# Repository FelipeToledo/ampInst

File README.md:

ampInst
=======

Repo para una placa amplificadora de bajo ruido para su uso en sismografos

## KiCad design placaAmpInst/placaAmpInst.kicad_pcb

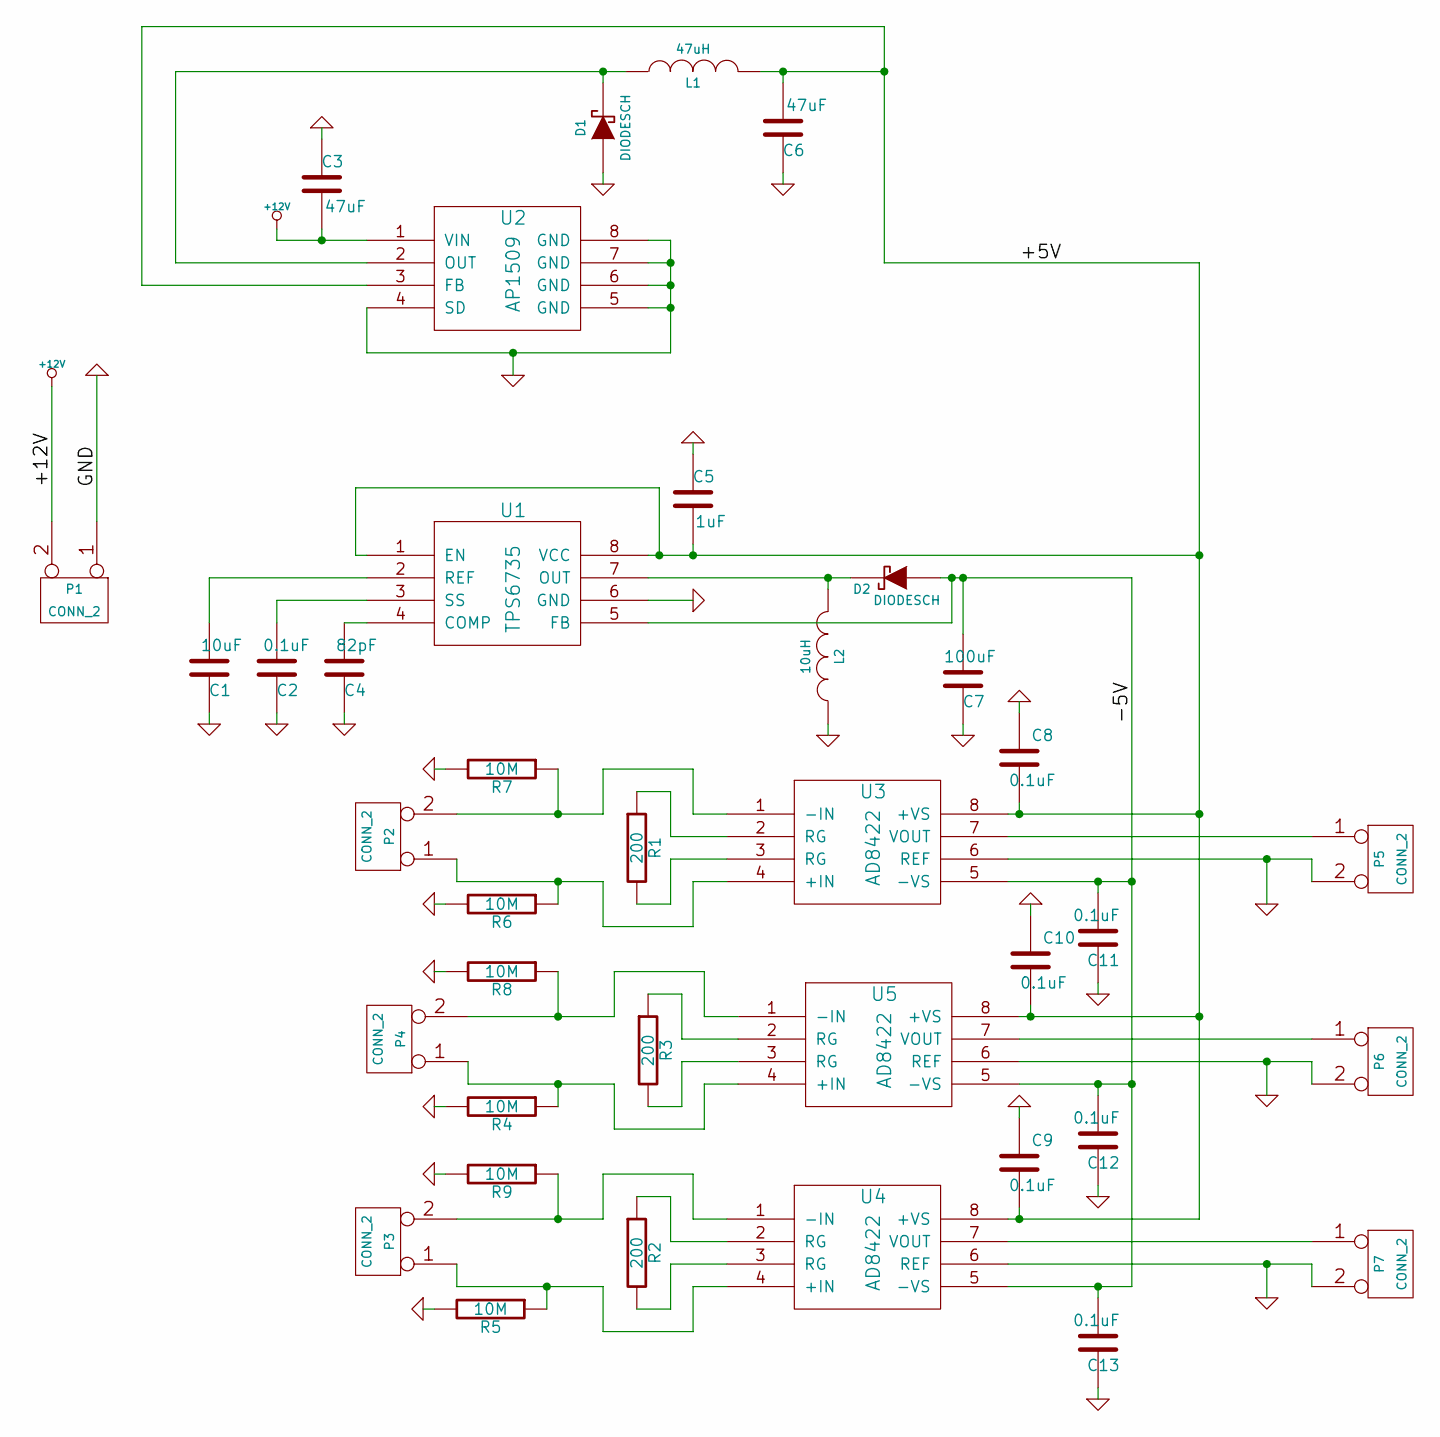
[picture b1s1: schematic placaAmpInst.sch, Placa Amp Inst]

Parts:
C1: 10uF
C2, C8, C9, C10, C11, C12, C13: 0.1uF
C3, C6: 47uF
C4: 82pF
C5: 1uF
C7: 100uF
D1, D2: DIODESCH
L1: 47uH
L2: 10uH
P1, P2, P3, P4, P5, P6, P7: CONN_2
R1, R2, R3: 200
R4, R5, R6, R7, R8, R9: 10M
U1: TPS6735
U2: AP1509
U3, U4, U5: AD8422

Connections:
+12V: C3.2, P1.2 (PM), U2.1 (VIN)
/+5V: C5.2, C6.2, C8.2, C9.2, C10.2, L1.2, U1.1 (EN), U1.8 (VCC), U2.3 (FB), U3.8 (+VS), U4.8 (+VS), U5.8 (+VS)
/-5V: C7.2, C11.2, C12.2, C13.2, D2.1 (A), U1.5 (FB), U3.5 (-VS), U4.5 (-VS), U5.5 (-VS)
GND: C1.1, C2.1, C3.1, C4.1, C5.1, C6.1, C7.1, C8.1, C9.1, C10.1, C11.1, C12.1, C13.1, D1.1 (A), L2.1, P1.1, P5.2 (PM), P6.2 (PM), P7.2 (PM), R4.2, R5.2, R6.2, R7.2, R8.2, R9.2, U1.6 (GND), U2.4 (SD), U2.5 (GND), U2.6 (GND), U2.7 (GND), U2.8 (GND), U3.6 (REF), U4.6 (REF), U5.6 (REF)
unnamed: C1.2, U1.2 (REF)
unnamed: C2.2, U1.3 (SS)
unnamed: C4.2, U1.4 (COMP)
unnamed: D1.2 (K), L1.1, U2.2 (OUT)
unnamed: D2.2 (K), L2.2, U1.7 (OUT)
unnamed: P2.1, R6.1, U3.4 (+IN)
unnamed: P2.2 (PM), R7.1, U3.1 (-IN)
unnamed: P3.1, R5.1, U4.4 (+IN)
unnamed: P3.2 (PM), R9.1, U4.1 (-IN)
unnamed: P4.1, R4.1, U5.4 (+IN)
unnamed: P4.2 (PM), R8.1, U5.1 (-IN)
unnamed: P5.1, U3.7 (VOUT)
unnamed: P6.1, U5.7 (VOUT)
unnamed: P7.1, U4.7 (VOUT)
unnamed: R1.1, U3.2 (RG)
unnamed: R1.2, U3.3 (RG)
unnamed: R2.1, U4.2 (RG)
unnamed: R2.2, U4.3 (RG)
unnamed: R3.1, U5.2 (RG)
unnamed: R3.2, U5.3 (RG)

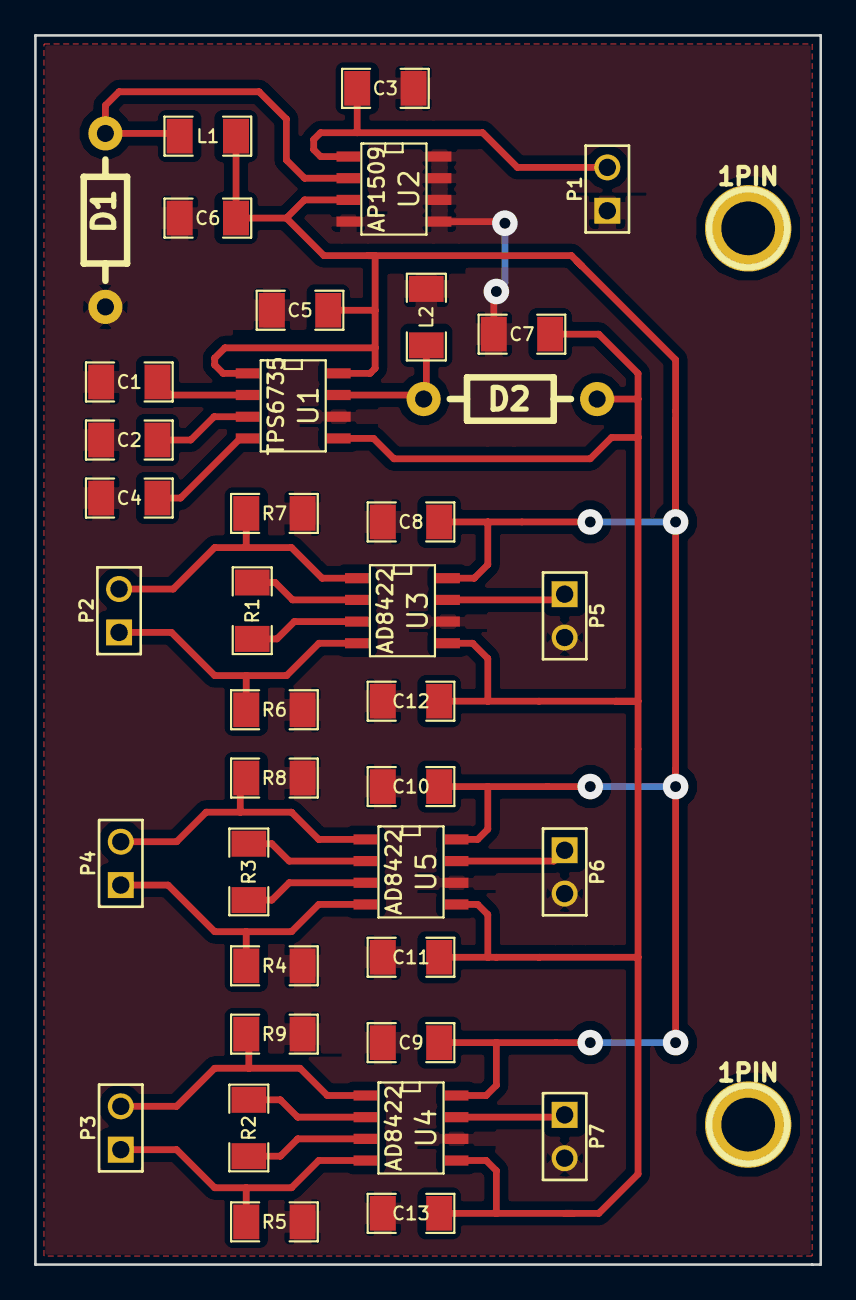
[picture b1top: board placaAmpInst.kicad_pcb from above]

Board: 2 copper layers, 46.0 x 72.0 mm, 40 parts (0 on the bottom side), 24 nets.

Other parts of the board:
1PIN, 1PIN#2: P***; 1pin

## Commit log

2013-12-02 deleted: README.md new file: readme.txt commit inicial para la placa amplificadora para sismografos#
2013-12-23 Se hace primer commit con la placa Amp lisa en un zip, pero con los archivos de Kicad con problemas en sus librerias. Por lo que se puede usar el zip apra fabricar placas , perop no Kicad>Gerber> Fob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
2013-12-26 Version que se mando a fabricar el 26 de Diiembre del 2013 Array es la version repetida (para la LPKF) de la placa de amplificacion.
